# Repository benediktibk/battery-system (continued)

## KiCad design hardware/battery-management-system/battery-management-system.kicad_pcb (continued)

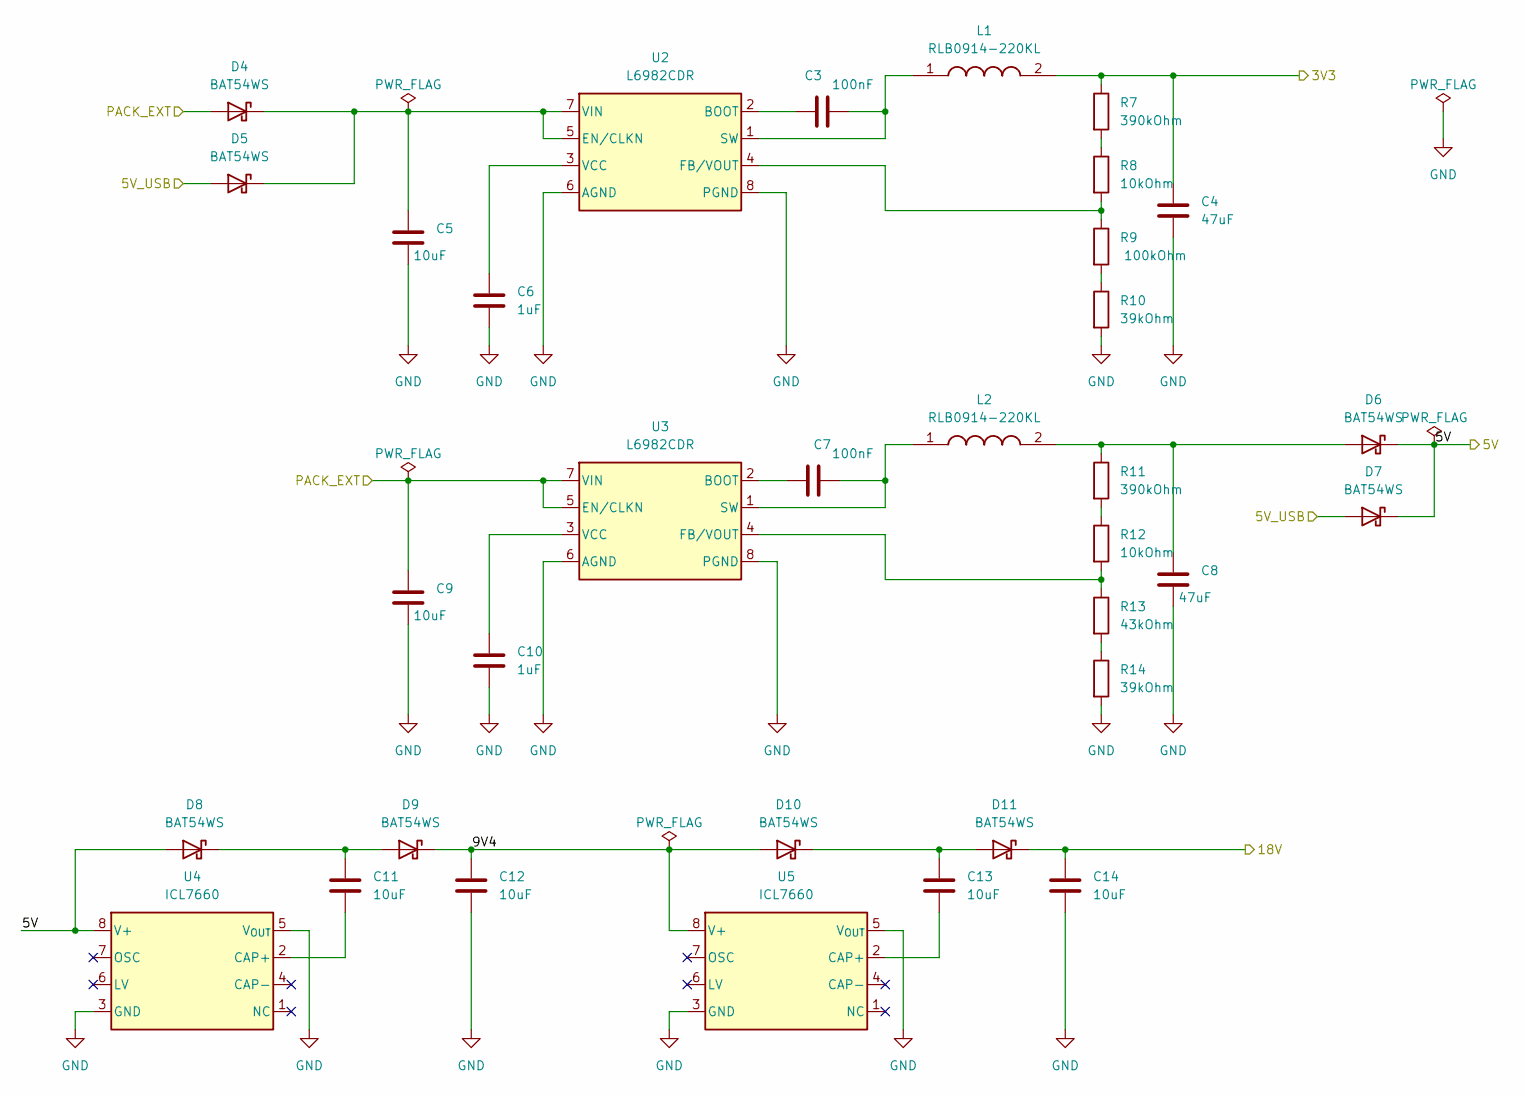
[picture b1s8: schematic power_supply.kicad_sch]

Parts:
C3, C7: 100nF; C_0603_1608Metric_Pad1.08x0.95mm_HandSolder; Mouser Part Number 581-KGM15BR71H104KM
C4, C8: 47uF; C_1206_3216Metric_Pad1.33x1.80mm_HandSolder; Mouser Part Number 810-C3216X5R1E476M
C5, C9, C11, C12, C13, C14: 10uF; C_1210_3225Metric_Pad1.33x2.70mm_HandSolder; Mouser Part Number 187-CL31A106MBHNNNE
C6, C10: 1uF; C_0603_1608Metric_Pad1.08x0.95mm_HandSolder; Mouser Part Number 963-UMK107BJ105KA-T
D4, D5, D6, D7, D8, D9, D10, D11: BAT54WS; D_SOD-323; Mouser Part Number 637-BAT54WS
L1, L2: RLB0914-220KL; RLB0914220KL; Mouser Part Number 652-RLB0914-220KL
R7, R11: 390kOhm; R_0603_1608Metric_Pad0.98x0.95mm_HandSolder; Mouser Part Number 603-RT0603FRE07390KL
R8, R12: 10kOhm; R_0603_1608Metric_Pad0.98x0.95mm_HandSolder; Mouser Part Number 652-CR0603FX-1002ELF
R9: 100kOhm; R_0603_1608Metric_Pad0.98x0.95mm_HandSolder; Mouser Part Number 603-RT0603FRE13100KL
R10, R14: 39kOhm; R_0603_1608Metric_Pad0.98x0.95mm_HandSolder; Mouser Part Number 603-RC0603FR-1039KL
R13: 43kOhm; R_0603_1608Metric_Pad0.98x0.95mm_HandSolder; Mouser Part Number 603-RT0603FRE0743KL
U2, U3: L6982CDR; SO-8_3.9x4.9mm_P1.27mm; Mouser Part Number 511-L6982CDR
U4, U5: ICL7660; SOIC-8_3.9x4.9mm_P1.27mm; Mouser Part Number 968-ICL7660CBAZ-T

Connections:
/3V3: C4.1, L1.2, R7.1; also elsewhere on the board
/5V: D6.1 (K), D7.1 (K), D8.2 (A), U4.8 (V+); also elsewhere on the board
/5V_USB: D5.2 (A), D7.2 (A); also elsewhere on the board
/18V: C14.1, D11.1 (K); also elsewhere on the board
/PACK_EXT: C9.1, D4.2 (A), U3.5 (EN/CLKN), U3.7 (VIN); also elsewhere on the board
/Power Supply/9V4: C12.1, D9.1 (K), D10.2 (A), U5.8 (V+)
GND: C4.2, C5.2, C6.2, C8.2, C9.2, C10.2, C12.2, C14.2, R10.2, R14.2, U2.6 (AGND), U2.8 (PGND), U3.6 (AGND), U3.8 (PGND), U4.3 (GND), U4.5 (V_{OUT}), U5.3 (GND), U5.5 (V_{OUT}); also elsewhere on the board
unnamed: C5.1, D4.1 (K), D5.1 (K), U2.5 (EN/CLKN), U2.7 (VIN)
unnamed: C8.1, D6.2 (A), L2.2, R11.1
unnamed: C11.1, D8.1 (K), D9.2 (A)
unnamed: C13.1, D10.1 (K), D11.2 (A)
unnamed: R7.2, R8.1
unnamed: R9.2, R10.1
unnamed: R11.2, R12.1
unnamed: R13.2, R14.1
unnamed: C3.2, U2.2 (BOOT)
unnamed: R8.2, R9.1, U2.4 (FB/VOUT)
unnamed: C3.1, L1.1, U2.1 (SW)
unnamed: C6.1, U2.3 (VCC)
unnamed: C7.2, U3.2 (BOOT)
unnamed: R12.2, R13.1, U3.4 (FB/VOUT)
unnamed: C7.1, L2.1, U3.1 (SW)
unnamed: C10.1, U3.3 (VCC)
unnamed: C11.2, U4.2 (CAP+)
unnamed: C13.2, U5.2 (CAP+)

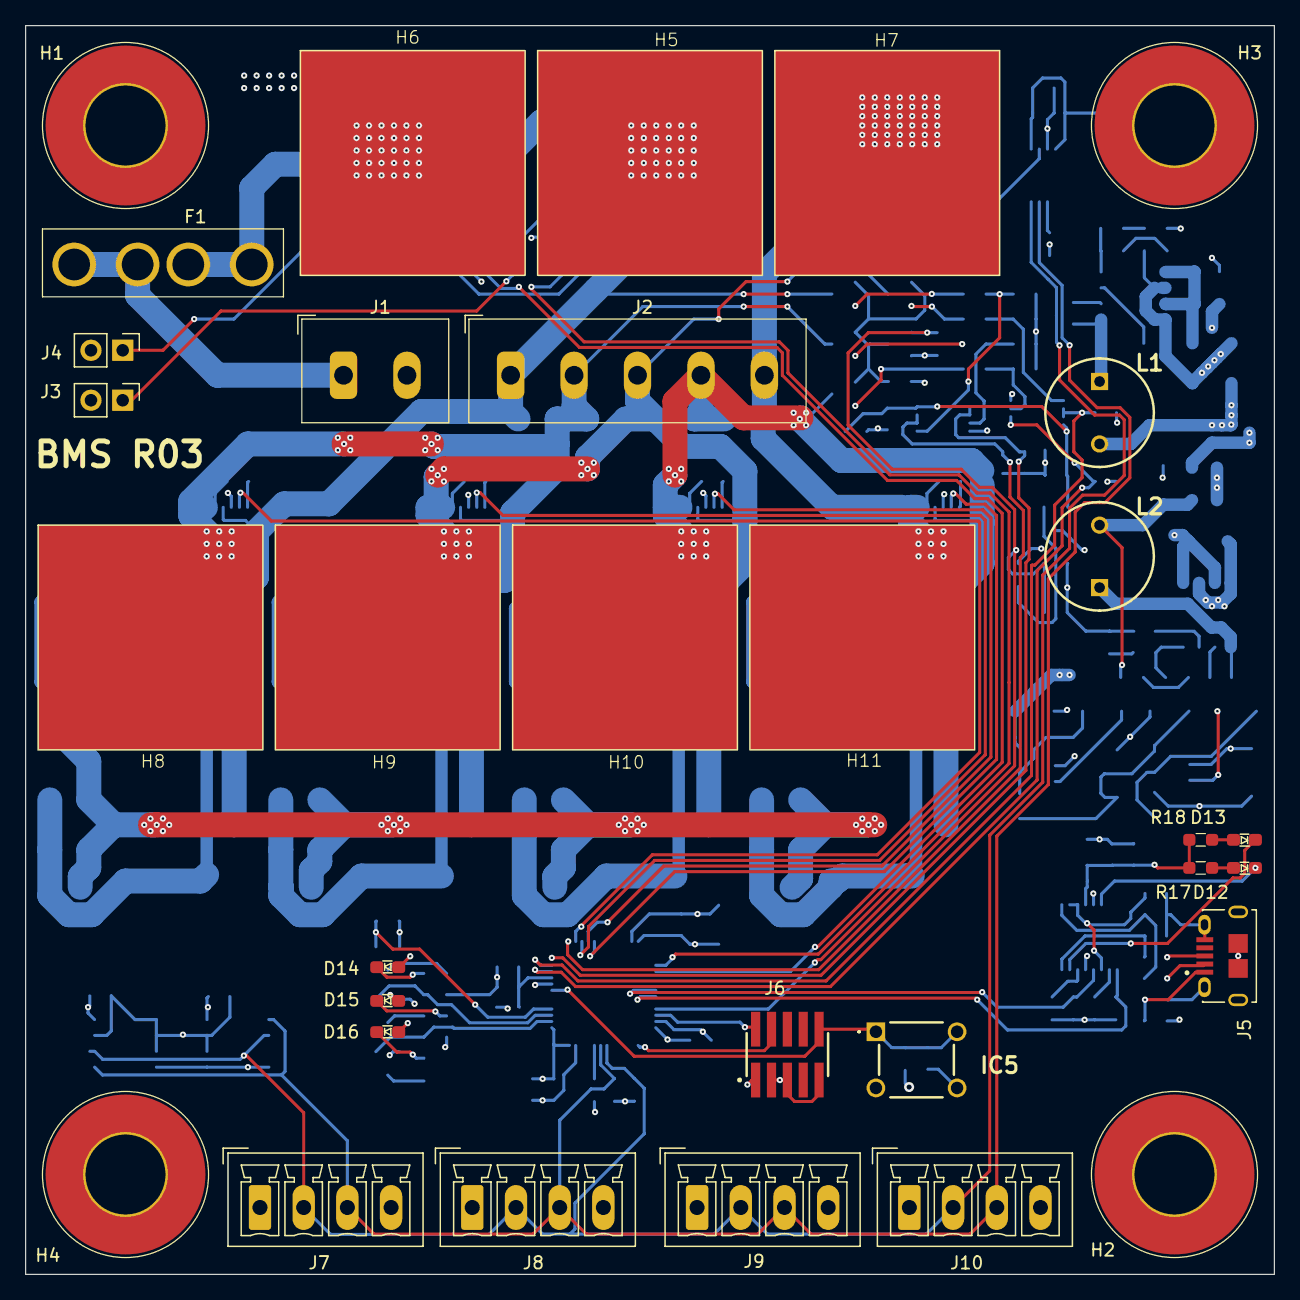
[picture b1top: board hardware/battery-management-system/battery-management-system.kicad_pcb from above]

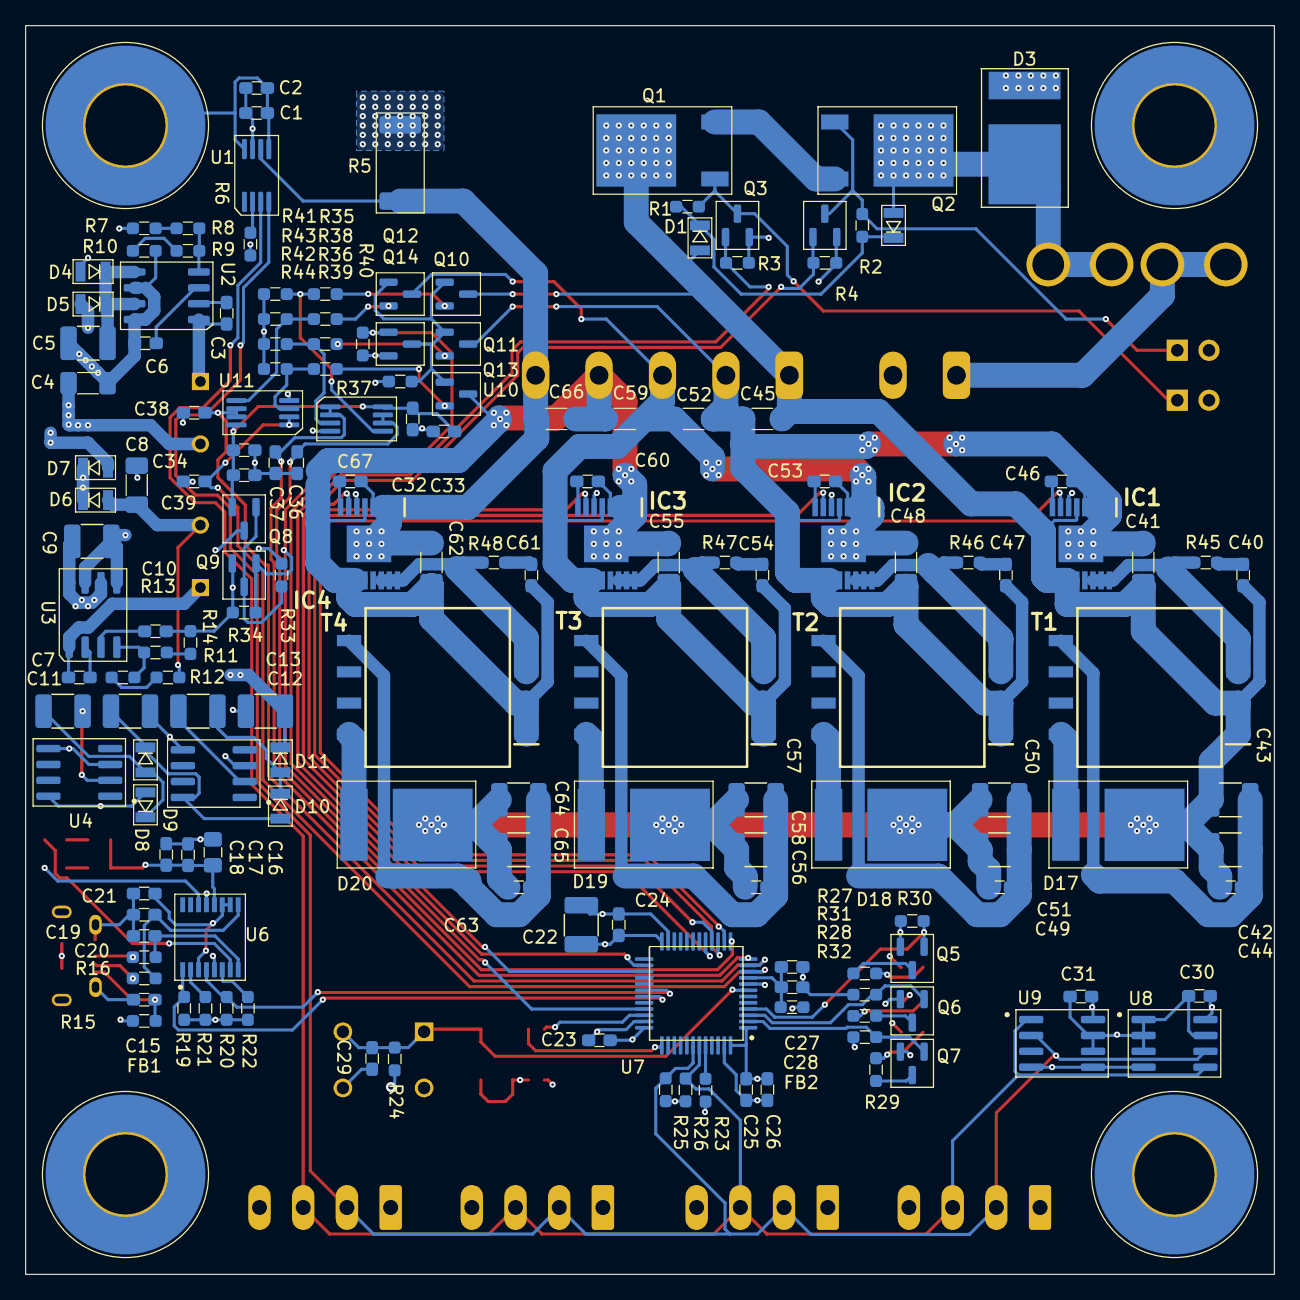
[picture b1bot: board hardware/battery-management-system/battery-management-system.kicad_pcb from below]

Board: 4 copper layers, 100.0 x 100.0 mm, 195 parts (163 on the bottom side), 108 nets.

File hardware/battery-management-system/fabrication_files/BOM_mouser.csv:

"Reference","Value","Qty","Mouser Part Number","RS order number"
"C1,C3,C7,C17,C18,C21,C23,C24,C25,C26,C27,C29,C30,C31,C32,C34,C36,C37,C38,C39","100nF","20","581-KGM15BR71H104KM","242-7372"
"C2,C6,C10,C28,C33,C35,C42,C49,C56,C63","1uF","10","963-UMK107BJ105KA-T","103-4112"
"C4,C8,C41,C45,C48,C52,C55,C59,C62,C66","47uF","10","810-C3216X5R1E476M","788-3060"
"C5,C9,C11,C12,C13,C14,C22,C43,C44,C50,C51,C57,C58,C64,C65","10uF","15","187-CL31A106MBHNNNE","172-1575"
"C15","10nF","1","80-C0603C103M5R3121","135-6315"
"C16","4.7uF","1","187-CL21A475KBQNNNE","113-8707"
"C19,C20","47pF","2","791-0603N470J101CT","135-6508"
"C40,C47,C54,C61","22nF","4","80-C0603C223K4R",""
"C46,C53,C60,C67","47nF","4","80-C0603C473K4RAC",""
"D1,D2,D4,D5,D6,D7,D8,D9,D10,D11","BAT54WS","10","637-BAT54WS","738-4844"
"D3,D17,D18,D19,D20","SBR2065D1","5","621-SBR2065D1-13","133-3329"
"D12","UART_TX","1","604-AP1608SGC","466-3706"
"D13","UART_RX","1","604-APH1608SURCK","861-0090"
"D14","green","1","604-AP1608SGC","466-3706"
"D15","red","1","604-APH1608SURCK","861-0090"
"D16","yellow","1","604-APG1608SYKC/T","861-0087"
"F1","20A","1","","167-6068"
"FB1,FB2","BLM18P","2","81-BLM11P300S","724-1403"
"H1,H2,H3,H4","MountingHole_Pad","4","",""
"H5,H6,H7,H8,H9,H10,H11","heatsink_18x18","7","490-HSB06-181810",""
"IC1,IC2,IC3,IC4","LT8584EFE#PBF","4","584-LT8584EFE#PBF",""
"IC5","RESET","1","179-TS026650BK100SCR",""
"J1","VBAT_DISCHARGE","1","","144-4347"
"J2","CELLS","1","","790-0966"
"J3","Charge","1","","251-8086"
"J4","Discharge","1","","251-8086"
"J5","AMPHENOL_micro_usb_10118194-0001LF","1","649-10118194-0001LF","137-0996"
"J6","ARM-JTAG-SWD","1","200-FTSH10501FDVK","159-2372"
"J7","TEMP_CELL1","1","","897-1039"
"J8","TEMP_CELL2","1","","897-1039"
"J9","TEMP_CELL3","1","","897-1039"
"J10","TEMP_CELL4","1","","897-1039"
"L1,L2","RLB0914-220KL","2","652-RLB0914-220KL",""
"Q1,Q2","TJ40S04M3L","2","757-TJ40S04M3LT6L1NQ","171-2479"
"Q3,Q4,Q5,Q6,Q7,Q9,Q14","DMN3404L","7","621-DMN3404L-7","751-4171"
"Q8,Q10,Q11,Q12,Q13","BS250FTA","5","522-BS250FTA","215-6593"
"R1,R2,R3,R4,R33,R34,R37,R40","220kOhm","8","71-CRCW0603-220K-E3","678-9986"
"R5","2mOhm/5W","1","660-TLR3APSDTE2L00F7","231-3683"
"R6","200kOhm","1","667-ERA-3AEB204V","684-5537"
"R7,R11","390kOhm","2","603-RT0603FRE07390KL","679-0279"
"R8,R12,R19,R20,R21,R22,R23,R24,R30,R31,R32","10kOhm","11","652-CR0603FX-1002ELF","125-1173"
"R9,R35,R36,R38,R44","100kOhm","5","603-RT0603FRE13100KL","213-2531"
"R10,R14","39kOhm","2","603-RC0603FR-1039KL","679-0285"
"R13","43kOhm","1","603-RT0603FRE0743KL","679-0386"
"R15,R16","27Ohm","2","603-RC0603FR-0727RL","213-2058"
"R17,R18","120Ohm","2","603-RC0603FR-07120RL","199-5452"
"R25,R26,R45,R46,R47,R48","4.7kOhm","6","652-CR0603FX-4701ELF","901-3581"
"R27,R28,R29","100Ohm","3","279-CRGH0603F100R","125-1172"
"R39,R41","24kOhm","2","71-CRCW060324K0FKEAC","199-5507"
"R42","36kOhm","1","652-CR0603FX-3602ELF","199-5550"
"R43","68kOhm","1","603-RT0603FRE0768KL","199-5620"
"T1,T2,T3,T4","NA6252-ALD","4","994-NA6252-ALD",""
"U1","STC3100","1","511-STC3100IST","795-8779"
"U2,U3","L6982CDR","2","511-L6982CDR","228-2997"
"U4,U5","ICL7660","2","968-ICL7660CBAZ-T","197-2514"
"U6","FT230XS","1","895-FT230XS-R","757-0010"
"U7","STM32L071CZTx","1","511-STM32L071CZT6","196-2075"
"U8","AT24C512C","1","556-AT24C512C-SSHM-T","197-5331"
"U9","NCT75DR2G","1","863-NCT75DR2G","805-1854"
"U10,U11","LM2904M8-13","2","621-LM2904M8-13","133-3375"

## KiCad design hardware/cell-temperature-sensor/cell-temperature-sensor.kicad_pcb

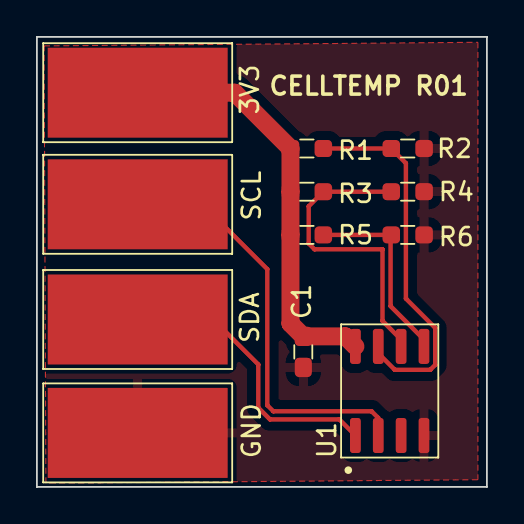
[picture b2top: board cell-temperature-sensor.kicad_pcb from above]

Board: 2 copper layers, 25.0 x 25.0 mm, 12 parts (0 on the bottom side), 7 nets.

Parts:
C1: 100nF; C_0603_1608Metric_Pad1.08x0.95mm_HandSolder
J1: 3V3; SolderWirePad_1x01_SMD_5x10mm
J2: SCL; SolderWirePad_1x01_SMD_5x10mm
J3: SDA; SolderWirePad_1x01_SMD_5x10mm
J4: GND; SolderWirePad_1x01_SMD_5x10mm
R1, R2, R3, R4, R5, R6: 100kOhm; R_0603_1608Metric_Pad0.98x0.95mm_HandSolder
U1: NCT75DR2G; SOIC-8_3.9x4.9mm_P1.27mm

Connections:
/3V3: C1.1, J1.1, R1.1, R3.1, R5.1, U1.8 (V_{CC})
/SCL: J2.1, U1.2 (SCL)
/SDA: J3.1, U1.1 (SDA)
GND: C1.2, J4.1, R2.2, R4.2, R6.2, U1.4 (GND)
unnamed: R1.2, R2.1, U1.7 (A0)
unnamed: R3.2, R4.1, U1.6 (A1)
unnamed: R5.2, R6.1, U1.5 (A2)

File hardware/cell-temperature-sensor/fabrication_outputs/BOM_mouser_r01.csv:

"Reference","Value","Qty","Mouser Part Number","RS order number"
"C1","100nF","1","581-KGM15BR71H104KM","242-7372"
"J1,J2,J3,J4","-- mixed values --","4","",""
"U1","NCT75DR2G","1","863-NCT75DR2G","805-1854"

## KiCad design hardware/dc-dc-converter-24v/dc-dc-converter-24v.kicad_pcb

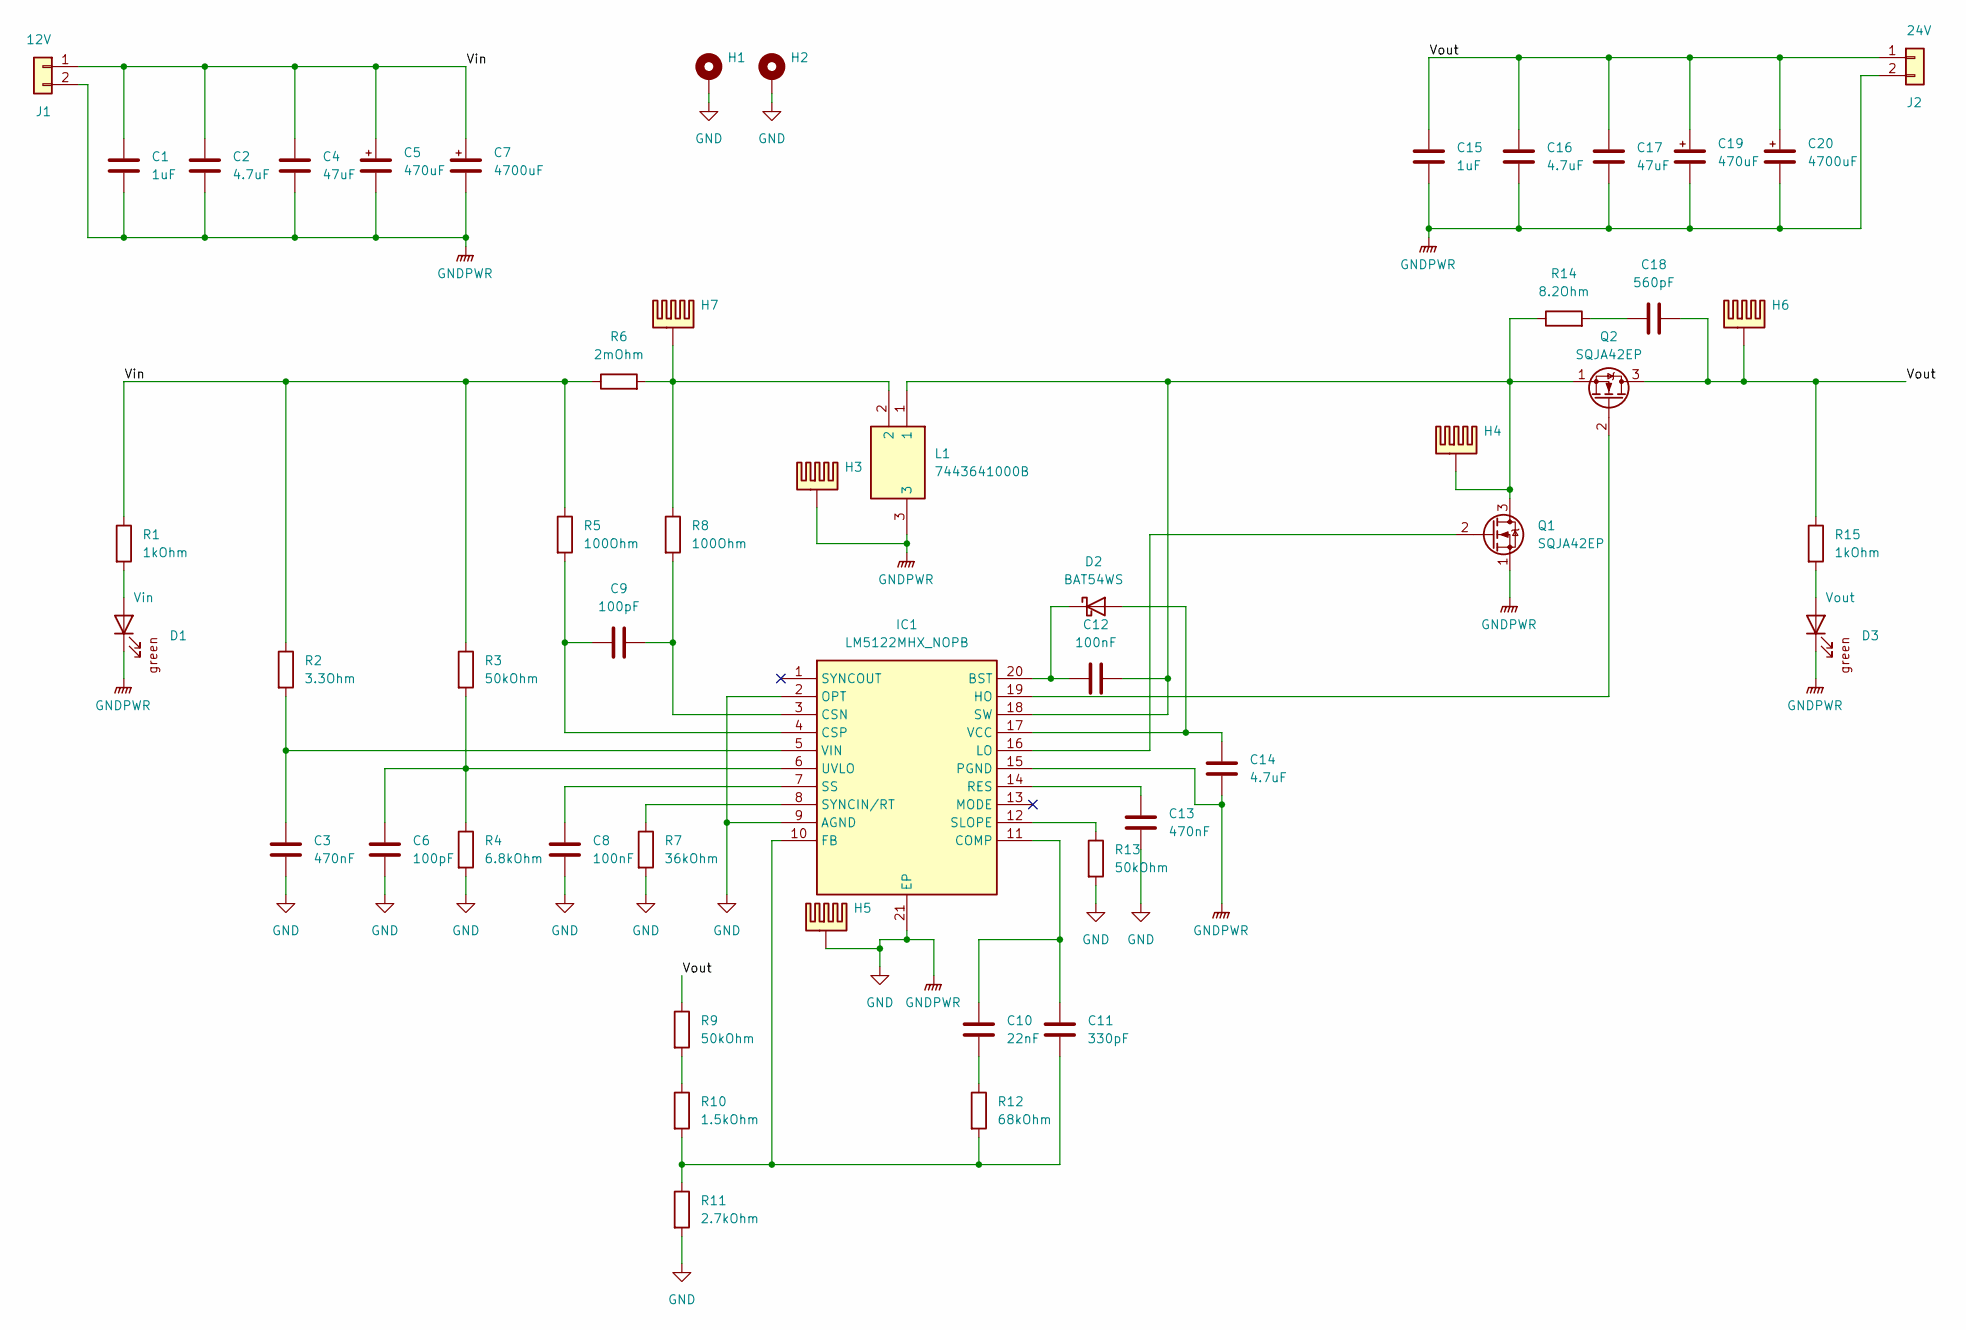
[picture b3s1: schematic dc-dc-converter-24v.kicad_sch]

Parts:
C1, C15: 1uF; C_0603_1608Metric_Pad1.08x0.95mm_HandSolder; Mouser Part Number 963-UMK107BJ105KA-T
C2, C14, C16: 4.7uF; C_0805_2012Metric_Pad1.18x1.45mm_HandSolder; Mouser Part Number 187-CL21A475KBQNNNE
C3, C13: 470nF; C_0603_1608Metric_Pad1.08x0.95mm_HandSolder; Mouser Part Number 963-TMK107B7474KA-TR
C4, C17: 47uF; C_1206_3216Metric_Pad1.33x1.80mm_HandSolder; Mouser Part Number 810-C3216X5R1E476M
C5, C19: 470uF; PCAP_16x16_5-ELECT_NCA-M; Mouser Part Number 647-UCD1J471MNQ1MS; Mouser order number 647-UCD1J471MNQ1MS
C6, C9: 100pF; C_0603_1608Metric_Pad1.08x0.95mm_HandSolder; Mouser Part Number 80-C0603C101K5GACLR
C7, C20: 4700uF; CP_Radial_D22.0mm_P10.00mm_SnapIn; Mouser Part Number 80-ESK478M050AQ3AA; Mouser order number 80-ESK478M050AQ3AA
C8, C12: 100nF; C_0603_1608Metric_Pad1.08x0.95mm_HandSolder; Mouser Part Number 581-KGM15BR71H104KM
C10: 22nF; C_0603_1608Metric_Pad1.08x0.95mm_HandSolder; Mouser Part Number 80-C0603C223K4R
C11: 330pF; C_0603_1608Metric_Pad1.08x0.95mm_HandSolder; Mouser Part Number 791-0603N331J500CT
C18: 560pF; C_0603_1608Metric_Pad1.08x0.95mm_HandSolder; Mouser Part Number 77-VJ0603A561JXAAC
D1: Vin; D_0603_1608Metric_Pad1.05x0.95mm_HandSolder; Mouser Part Number 604-AP1608SGC
D2: BAT54WS; D_SOD-323; Mouser Part Number 637-BAT54WS
D3: Vout; D_0603_1608Metric_Pad1.05x0.95mm_HandSolder; Mouser Part Number 604-AP1608SGC
H1, H2: MountingHole_Pad_M6; MountingHole_6.4mm_M6_Pad_TopBottom
H3, H4, H5, H6, H7: heatsink_18x18; Mouser Part Number 490-HSB06-181810; Mouser order number 490-HSB06-181810
IC1: LM5122MHX_NOPB; SOP65P640X110-21N; Mouser Part Number 595-LM5122MHX/NOPB
J1: 12V; rspro_header_2pin_5_08mm
J2: 24V; rspro_header_2pin_5_08mm
L1: 7443641000B; Mouser Part Number 710-7443641000B
Q1, Q2: SQJA42EP; SQJA42EPT1_GE3; Mouser Part Number 78-SQJA42EP-T1_GE3
R1, R15: 1kOhm; R_0603_1608Metric_Pad0.98x0.95mm_HandSolder; Mouser Part Number 603-RC0603FR-101KL
R2: 3.3Ohm; R_0603_1608Metric_Pad0.98x0.95mm_HandSolder; Mouser Part Number 603-RT0603BRD073R3L
R3, R9, R13: 50kOhm; R_0603_1608Metric_Pad0.98x0.95mm_HandSolder; Mouser Part Number 603-RT0603BRD0750KL
R4: 6.8kOhm; R_0603_1608Metric_Pad0.98x0.95mm_HandSolder; Mouser Part Number 594-MCT0603ME6801BP5
R5, R8: 100Ohm; R_0603_1608Metric_Pad0.98x0.95mm_HandSolder; Mouser Part Number 279-CRGH0603F100R
R6: 2mOhm; R_2512_6332Metric_Pad1.40x3.35mm_HandSolder; Mouser Part Number 660-TLR3APSDTE2L00F7
R7: 36kOhm; R_0603_1608Metric_Pad0.98x0.95mm_HandSolder; Mouser Part Number 652-CR0603FX-3602ELF
R10: 1.5kOhm; R_0603_1608Metric_Pad0.98x0.95mm_HandSolder; Mouser Part Number 667-ERA-3APB152V
R11: 2.7kOhm; R_0603_1608Metric_Pad0.98x0.95mm_HandSolder; Mouser Part Number 667-ERA-3ARB272V
R12: 68kOhm; R_0603_1608Metric_Pad0.98x0.95mm_HandSolder; Mouser Part Number 603-RT0603FRE0768KL
R14: 8.2Ohm; R_0603_1608Metric_Pad0.98x0.95mm_HandSolder; Mouser Part Number 660-RK73B1JTTD8R2J

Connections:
/Vin: C1.1, C2.1, C4.1, C5.1, C7.1, J1.1, R1.1, R2.1, R3.1, R5.1, R6.1
/Vout: C15.1, C16.1, C17.1, C18.2, C19.1, C20.1, H6.PAD, J2.1, Q2.3 (D), R9.1, R15.1
GND: C1.2, C2.2, C3.2, C4.2, C5.2, C6.2, C7.2, C8.2, C13.2, C14.2, C15.2, C16.2, C17.2, C19.2, C20.2, D1.1 (K), D3.1 (K), H1.1, H2.1, H3.PAD, H5.PAD, IC1.2 (OPT), IC1.9 (AGND), IC1.15 (PGND), IC1.21 (EP), J1.2, J2.2, L1.3, Q1.1 (S), R4.2, R7.2, R11.2, R13.2
unnamed: C10.2, R12.1
unnamed: C18.1, R14.2
unnamed: D1.2 (A), R1.2
unnamed: C14.1, D2.2 (A), IC1.17 (VCC)
unnamed: C12.1, D2.1 (K), IC1.20 (BST)
unnamed: D3.2 (A), R15.2
unnamed: H7.PAD, L1.2, R6.2, R8.1
unnamed: C10.1, C11.1, IC1.11 (COMP)
unnamed: C9.2, IC1.3 (CSN), R8.2
unnamed: C9.1, IC1.4 (CSP), R5.2
unnamed: C11.2, IC1.10 (FB), R10.2, R11.1, R12.2
unnamed: IC1.19 (HO), Q2.2 (G)
unnamed: IC1.16 (LO), Q1.2 (G)
unnamed: C13.1, IC1.14 (RES)
unnamed: IC1.12 (SLOPE), R13.1
unnamed: C8.1, IC1.7 (SS)
unnamed: C12.2, H4.PAD, IC1.18 (SW), L1.1, Q1.3 (D), Q2.1 (S), R14.1
unnamed: IC1.8 (SYNCIN/RT), R7.1
unnamed: C6.1, IC1.6 (UVLO), R3.2, R4.1
unnamed: C3.1, IC1.5 (VIN), R2.2
unnamed: R9.2, R10.1

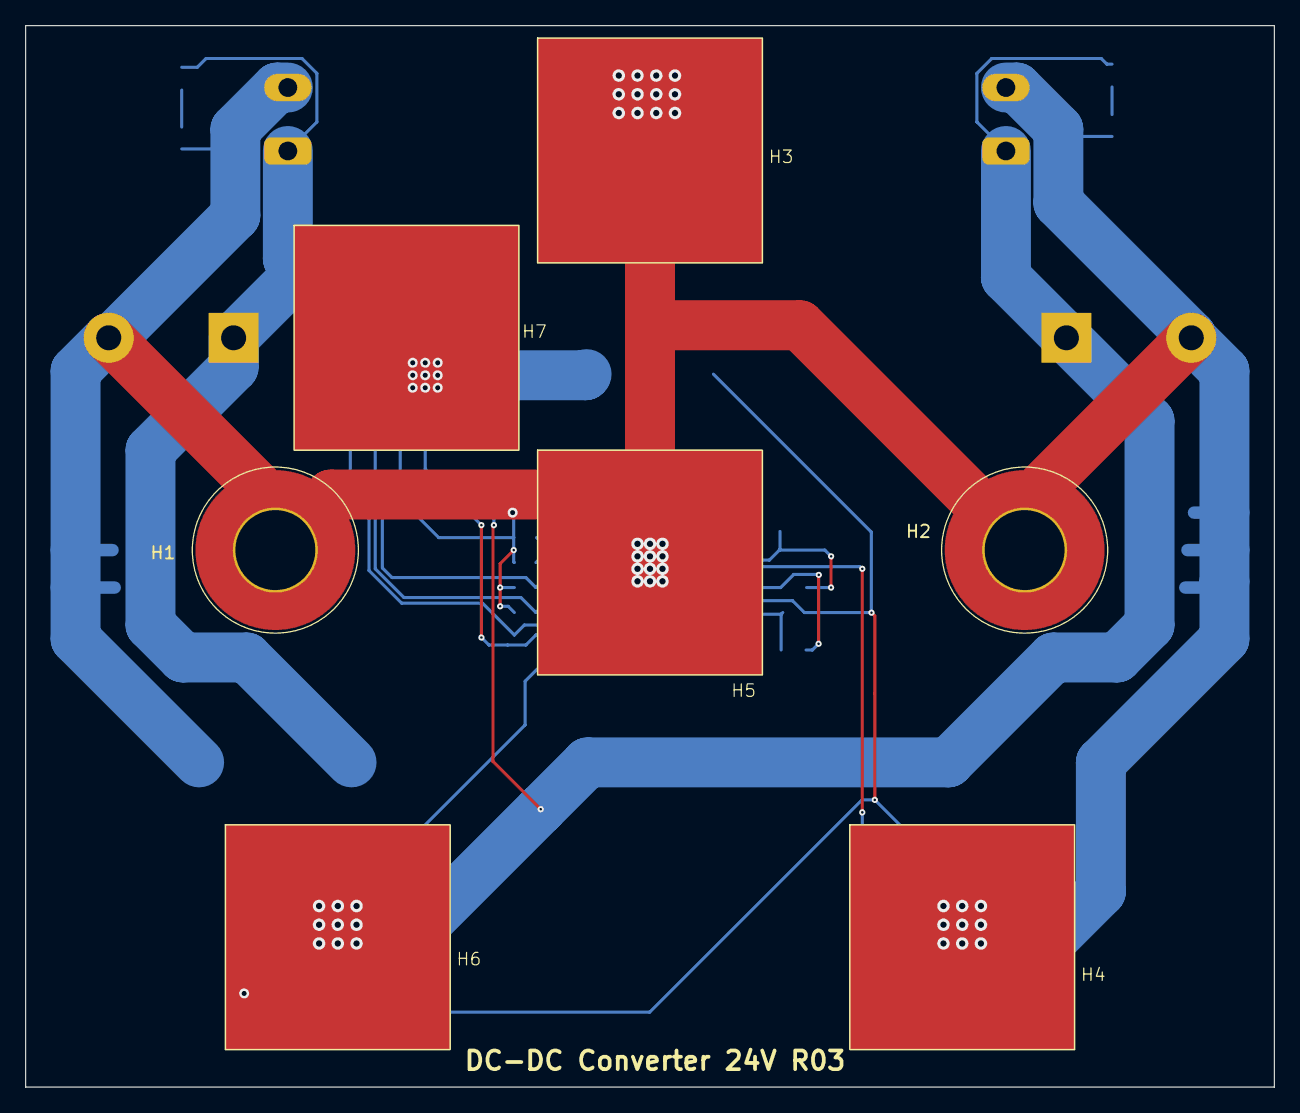
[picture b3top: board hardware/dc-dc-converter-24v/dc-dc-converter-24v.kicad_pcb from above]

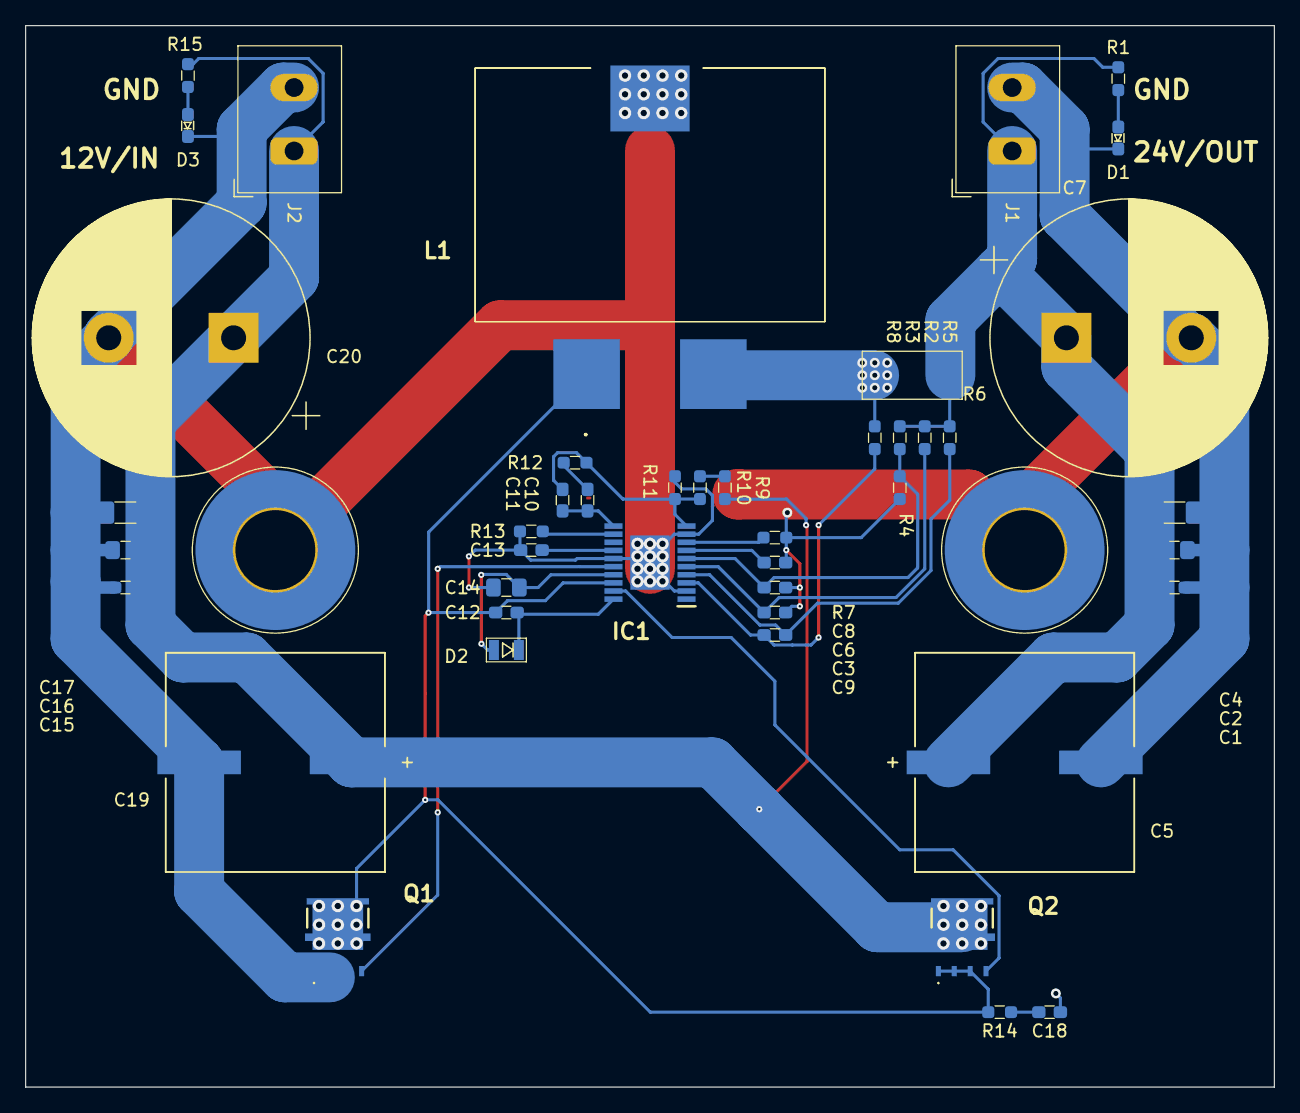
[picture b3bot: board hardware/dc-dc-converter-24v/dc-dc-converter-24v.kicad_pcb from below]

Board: 2 copper layers, 100.0 x 85.0 mm, 51 parts (44 on the bottom side), 24 nets.

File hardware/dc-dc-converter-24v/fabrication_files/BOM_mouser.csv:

"Reference","Value","Qty","Mouser Part Number","RS order number"
"C1,C15","1uF","2","963-UMK107BJ105KA-T","103-4112"
"C2,C14,C16","4.7uF","3","187-CL21A475KBQNNNE","113-8707"
"C3,C13","470nF","2","963-TMK107B7474KA-TR",""
"C4,C17","47uF","2","810-C3216X5R1E476M","788-3060"
"C5,C19","470uF","2","647-UCD1J471MNQ1MS ","243-7225"
"C6,C9","100pF","2","80-C0603C101K5GACLR",""
"C7,C20","4700uF","2","80-ESK478M050AQ3AA",""
"C8,C12","100nF","2","581-KGM15BR71H104KM","242-7372"
"C10","22nF","1","80-C0603C223K4R",""
"C11","330pF","1","791-0603N331J500CT ",""
"C18","560pF","1","77-VJ0603A561JXAAC","135-6233"
"D1,D3","-- mixed values --","2","604-AP1608SGC","466-3706"
"D2","BAT54WS","1","637-BAT54WS","738-4844"
"H1,H2,J1,J2","-- mixed values --","4","","-- mixed values --"
"H3,H4,H5,H6,H7","~","5","490-HSB06-181810",""
"IC1","LM5122MHX_NOPB","1","595-LM5122MHX/NOPB",""
"L1","7443641000B","1","710-7443641000B",""
"Q1,Q2","SQJA42EP","2","78-SQJA42EP-T1_GE3","188-5140"
"R1,R15","1kOhm","2","603-RC0603FR-101KL","213-2266"
"R2","3.3Ohm","1","603-RT0603BRD073R3L",""
"R3,R9,R13","50kOhm","3","603-RT0603BRD0750KL ",""
"R4","6.8kOhm","1","594-MCT0603ME6801BP5",""
"R5,R8","100Ohm","2","279-CRGH0603F100R","125-1172"
"R6","2mOhm","1","660-TLR3APSDTE2L00F7","231-3683"
"R7","36kOhm","1","652-CR0603FX-3602ELF","199-5550"
"R10","1.5kOhm","1","667-ERA-3APB152V",""
"R11","2.7kOhm","1","667-ERA-3ARB272V",""
"R12","68kOhm","1","603-RT0603FRE0768KL","199-5620"
"R14","8.2Ohm","1","660-RK73B1JTTD8R2J ",""

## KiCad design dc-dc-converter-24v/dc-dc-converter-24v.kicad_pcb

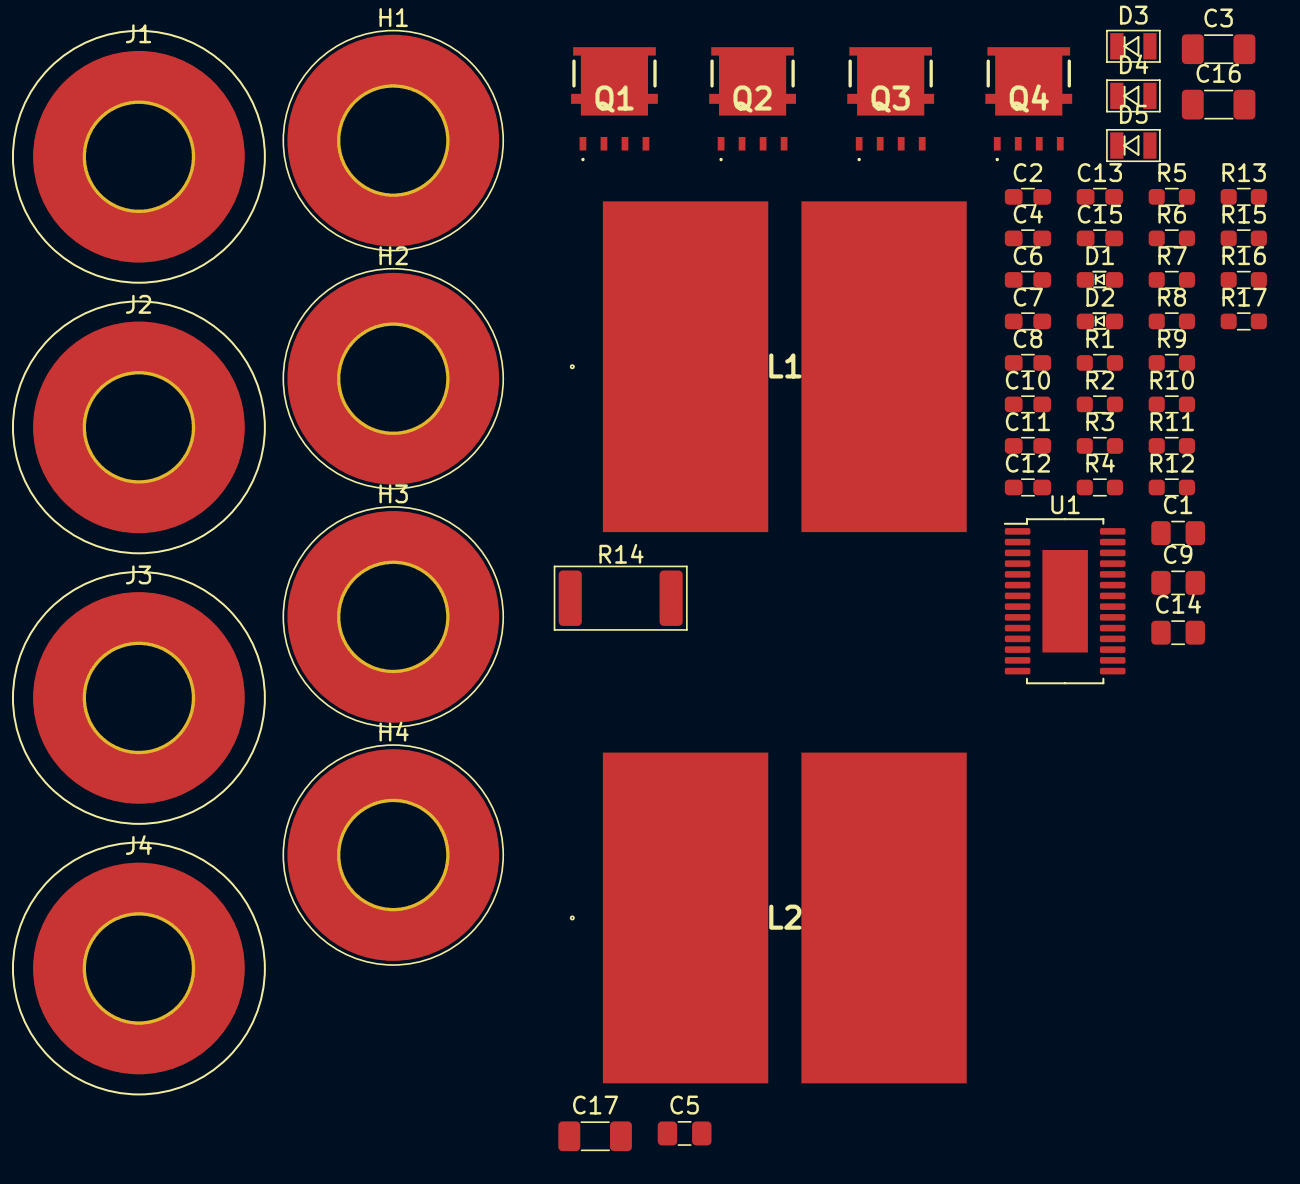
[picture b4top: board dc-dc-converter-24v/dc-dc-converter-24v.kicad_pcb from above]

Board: 2 copper layers, 54 parts (0 on the bottom side), 32 nets, no tracks yet.

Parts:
C1, C5, C14: 4.7uF; C_0805_2012Metric_Pad1.18x1.45mm_HandSolder
C2, C4, C7, C11, C12: 100nF; C_0603_1608Metric_Pad1.08x0.95mm_HandSolder
C3, C16, C17: 47uF; C_1206_3216Metric_Pad1.33x1.80mm_HandSolder
C6, C13: 1uF; C_0603_1608Metric_Pad1.08x0.95mm_HandSolder
C8: 560pF; C_0603_1608Metric_Pad1.08x0.95mm_HandSolder
C9: 240pF; C_0805_2012Metric_Pad1.18x1.45mm_HandSolder
C10: 33nF; C_0603_1608Metric_Pad1.08x0.95mm_HandSolder
C15: 47pF; C_0603_1608Metric_Pad1.08x0.95mm_HandSolder
D1: Vin; D_0603_1608Metric_Pad1.05x0.95mm_HandSolder
D2: Vout good; D_0603_1608Metric_Pad1.05x0.95mm_HandSolder
D3, D4, D5: BAT54WS; D_SOD-323
H1, H2, H3, H4: MountingHole_Pad_M6; MountingHole_6.4mm_M6_Pad_TopBottom
J1: 24V; Connector_M6
J2: 12V; Connector_M6
J3, J4: GND; Connector_M6
L1, L2: 2.5µH; ETQP8
Q1, Q2, Q3, Q4: SQJA42EP; SQJA42EPT1_GE3
R1, R2: 1kOhm; R_0603_1608Metric_Pad0.98x0.95mm_HandSolder
R3, R11, R15: 10kOhm; R_0603_1608Metric_Pad0.98x0.95mm_HandSolder
R4: 24kOhm; R_0603_1608Metric_Pad0.98x0.95mm_HandSolder
R5: 93.1kOhm; R_0603_1608Metric_Pad0.98x0.95mm_HandSolder
R6: 220kOhm; R_0603_1608Metric_Pad0.98x0.95mm_HandSolder
R7: 43kOhm; R_0603_1608Metric_Pad0.98x0.95mm_HandSolder
R8: 0Ohm; R_0603_1608Metric_Pad0.98x0.95mm_HandSolder
R9: 2kOhm; R_0603_1608Metric_Pad0.98x0.95mm_HandSolder
R10: 10Ohm; R_0603_1608Metric_Pad0.98x0.95mm_HandSolder
R12, R13: 100Ohm; R_0603_1608Metric_Pad0.98x0.95mm_HandSolder
R14: 4mOhm; R_2512_6332Metric_Pad1.40x3.35mm_HandSolder
R16: 20kOhm; R_0603_1608Metric_Pad0.98x0.95mm_HandSolder
R17: 270kOhm; R_0603_1608Metric_Pad0.98x0.95mm_HandSolder
U1: LM5176

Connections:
/Boost Converter/12V: C13.1, C14.1, C16.1, D3.2 (A), J2.1, Q2.3 (D), R1.1, R2.1, R6.1, R9.1
/Boost Converter/Vcc: C6.1, D4.2 (A), D5.2 (A), R3.1, U1.23 (VCC)
/Boost Converter/Vout: C1.1, C2.1, C3.1, L2.1, Q4.3 (D), R16.1, U1.12 (VOSNS), U1.24 (BIAS)
/Output Filter/24VFILT: C5.1, C17.1, J1.1, L2.2
GND: C1.2, C2.2, C3.2, C4.2, C5.2, C6.2, C7.2, C8.2, C9.2, C13.2, C14.2, C16.2, C17.2, D1.1 (K), J3.1, J4.1, R4.2, R5.1, R7.2, R8.2, R11.2, R13.2, R14.2, R15.2, U1.10 (AGND), U1.13 (ISNS-), U1.14 (ISNS+), U1.22 (PGND), U1.29 (PAD)
unnamed: C10.2, R11.1
unnamed: D1.2 (A), R1.2
unnamed: D2.2 (A), R2.2
unnamed: D2.1 (K), R3.2, U1.17 (PGOOD)
unnamed: D3.1 (K), R10.1
unnamed: C11.1, D4.1 (K), U1.26 (BOOT1)
unnamed: C12.1, D5.1 (K), U1.20 (BOOT2)
unnamed: C11.2, L1.1, Q1.3 (D), Q2.1 (S), U1.28 (SW1)
unnamed: Q1.2 (G), U1.25 (LDRV1)
unnamed: Q1.1 (S), Q3.1 (S), R12.2, R14.1
unnamed: Q2.2 (G), U1.27 (HDRV1)
unnamed: L1.2, Q3.3 (D), Q4.1 (S)
unnamed: C12.2, Q3.2 (G), U1.18 (SW2)
unnamed: Q4.2 (G), U1.19 (HDRV2)
unnamed: R16.2, R17.1
unnamed: C8.1, C10.1, U1.9 (COMP)
unnamed: C15.1, R12.1, U1.16 (CS)
unnamed: C15.2, R13.1, U1.15 (CSG)
unnamed: R8.1, U1.5 (DITH)
unnamed: R6.2, R7.1, U1.1 (EN/UVLO)
unnamed: R15.1, R17.2, U1.11 (FB)
unnamed: R5.2, U1.4 (MODE)
unnamed: R4.1, U1.6 (RT/SYNC)
unnamed: C9.1, U1.7 (SLOPE)
unnamed: C4.1, U1.8 (SS)
unnamed: C7.1, R10.2, U1.2 (VIN)
unnamed: R9.2, U1.3 (VISNS)
